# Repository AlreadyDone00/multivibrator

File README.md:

# *Шифр проекта*
мультивибратор
## Features: разъем J1 - питание +5V
## 3d model:

## dimensional drawing:

## characteristics:
voltage input 5V
## Changelog:
### v 1.0
- Init

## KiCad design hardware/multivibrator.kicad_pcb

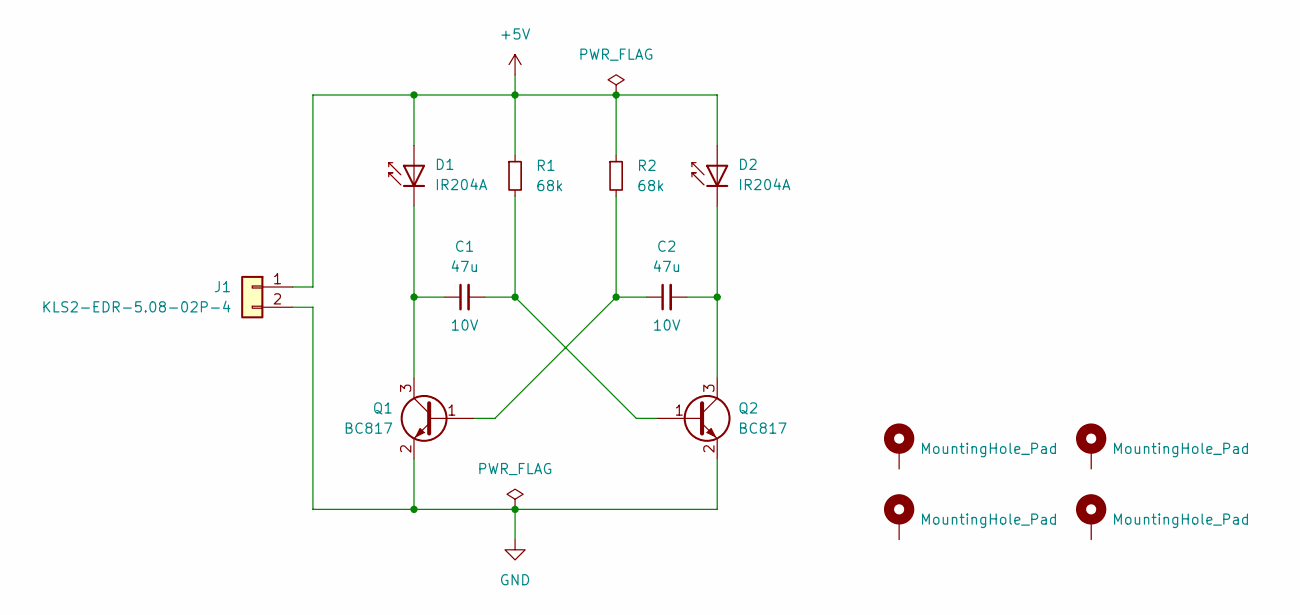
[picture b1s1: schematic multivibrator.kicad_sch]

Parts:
C1, C2: 47u; C_0805_2012Metric; Voltage 10V; lcsc C6119904
D1, D2: IR204A; LED_D3.0mm_IRBlack; lcsc C264278
H1, H2, H3, H4: MountingHole_Pad; MountingHole_3.2mm_M3_DIN965_Pad
J1: KLS2-EDR-5.08-02P-4
Q1, Q2: BC817; SOT-23; lcsc C5249694
R1, R2: 68k; R_0805_2012Metric; lcsc C17801

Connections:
+5V: D1.2 (A), D2.2 (A), J1.1, R1.1, R2.1
GND: J1.2, Q1.2 (E), Q2.2 (E)
unnamed: C1.1, D1.1 (K), Q1.3 (C)
unnamed: C2.2, D2.1 (K), Q2.3 (C)
unnamed: C2.1, Q1.1 (B), R2.2
unnamed: C1.2, Q2.1 (B), R1.2

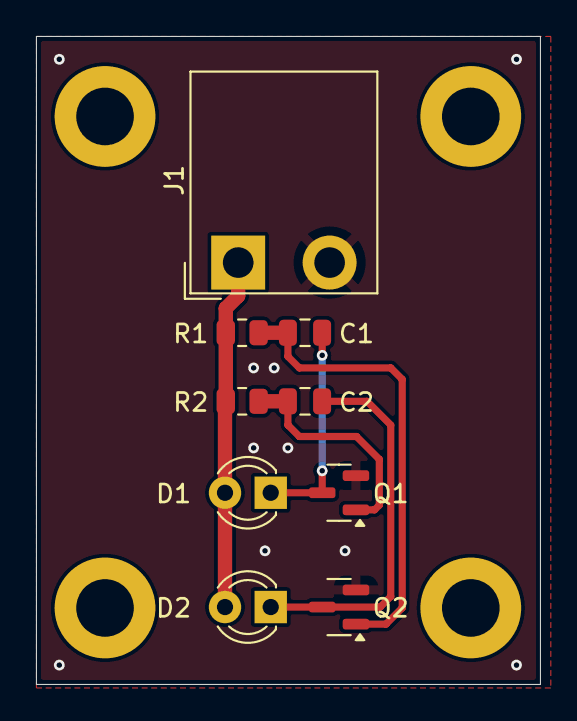
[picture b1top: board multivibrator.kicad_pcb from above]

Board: 2 copper layers, 28.0 x 36.0 mm, 13 parts (0 on the bottom side), 6 nets.

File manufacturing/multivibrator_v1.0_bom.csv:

"Reference","Value","Datasheet","Footprint","Qty","DNP","Voltage","chipdip","lcsc","coefficient"
"C1,C2","47u","~","Capacitor_SMD:C_0805_2012Metric","2","","10V","9000326168","C6119904",""
"R1,R2","68k","~","Resistor_SMD:R_0805_2012Metric","2","","","9000189877","C17801","5%"
"Q1,Q2","BC817","https://www.onsemi.com/pub/Collateral/BC818-D.pdf","Package_TO_SOT_SMD:SOT-23","2","","","28806907"," C5249694",""
"D1,D2","IR204A","http://www.everlight.com/file/ProductFile/IR204-A.pdf","LED_THT:LED_D3.0mm_IRBlack","2","","","8023113118","C264278",""
"J1","KLS2-EDR-5.08-02P-4","https://static.chipdip.ru/lib/507/DOC001507222.pdf","MAS_Package_nostd:KLS2-EDR-5.08-02P-4","1","","","9000603329","",""

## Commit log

2024-09-03 Создана схема
2024-09-04 Создана схема
    Изменена структура проекта
2024-09-04 создан .gitignore
2024-09-04 Создана печатная плата
2024-09-05 Добавлены монтажные отверстия
    + изменена структура репозитория
2024-09-05 update gitignore
2024-09-05 учтены замечания
2024-09-06 приняты новые рекомендации
2024-09-06 создан gerber
